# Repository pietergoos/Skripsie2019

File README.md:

# Skripsie2019
Final year project / Thesis

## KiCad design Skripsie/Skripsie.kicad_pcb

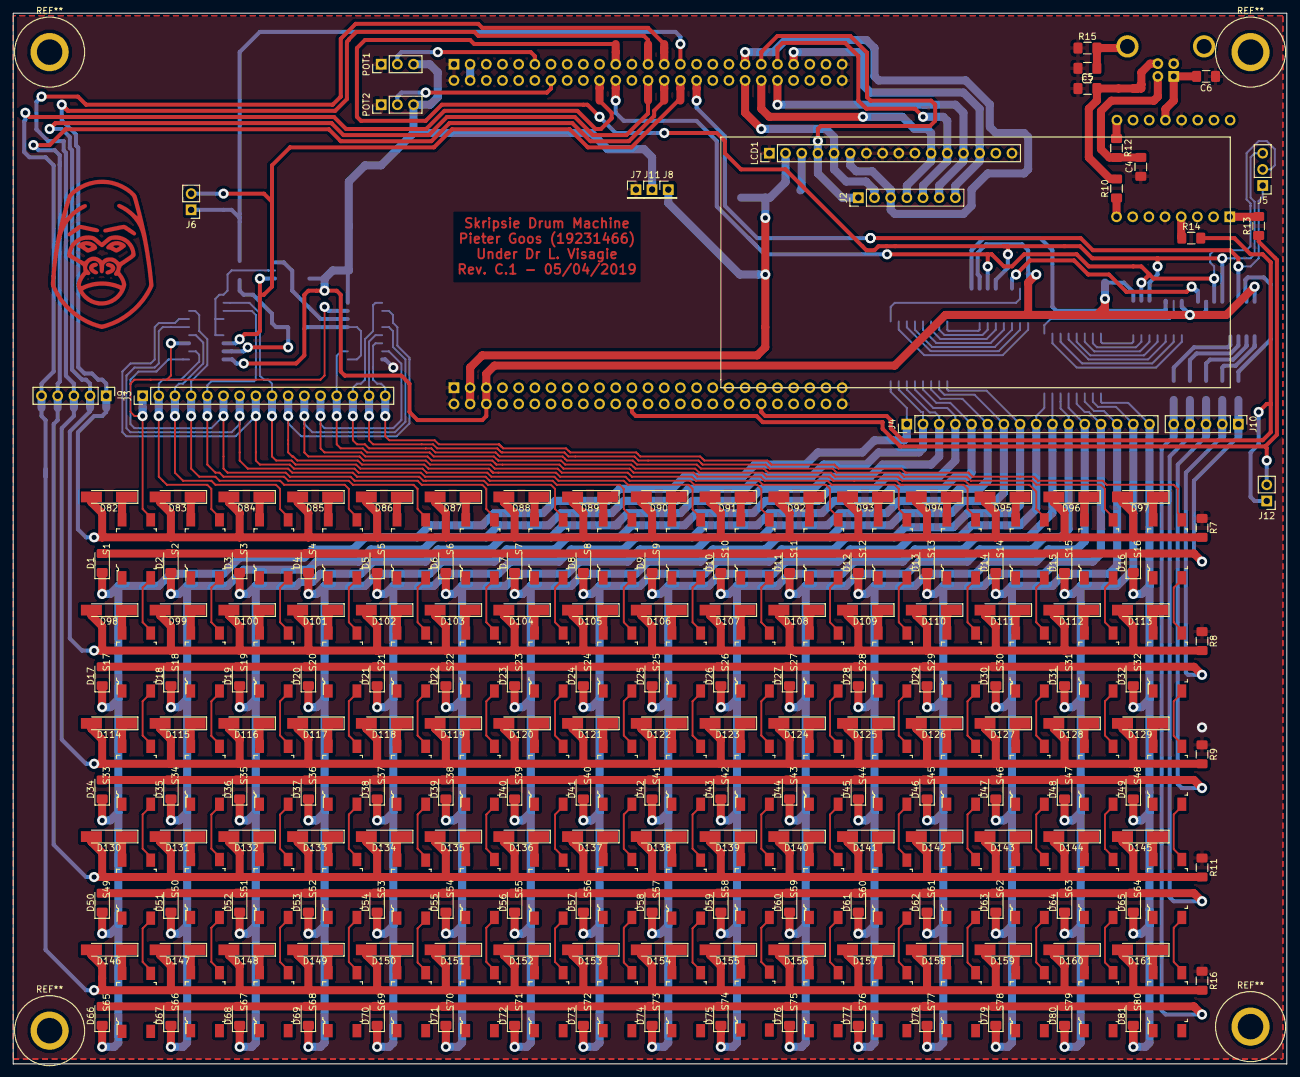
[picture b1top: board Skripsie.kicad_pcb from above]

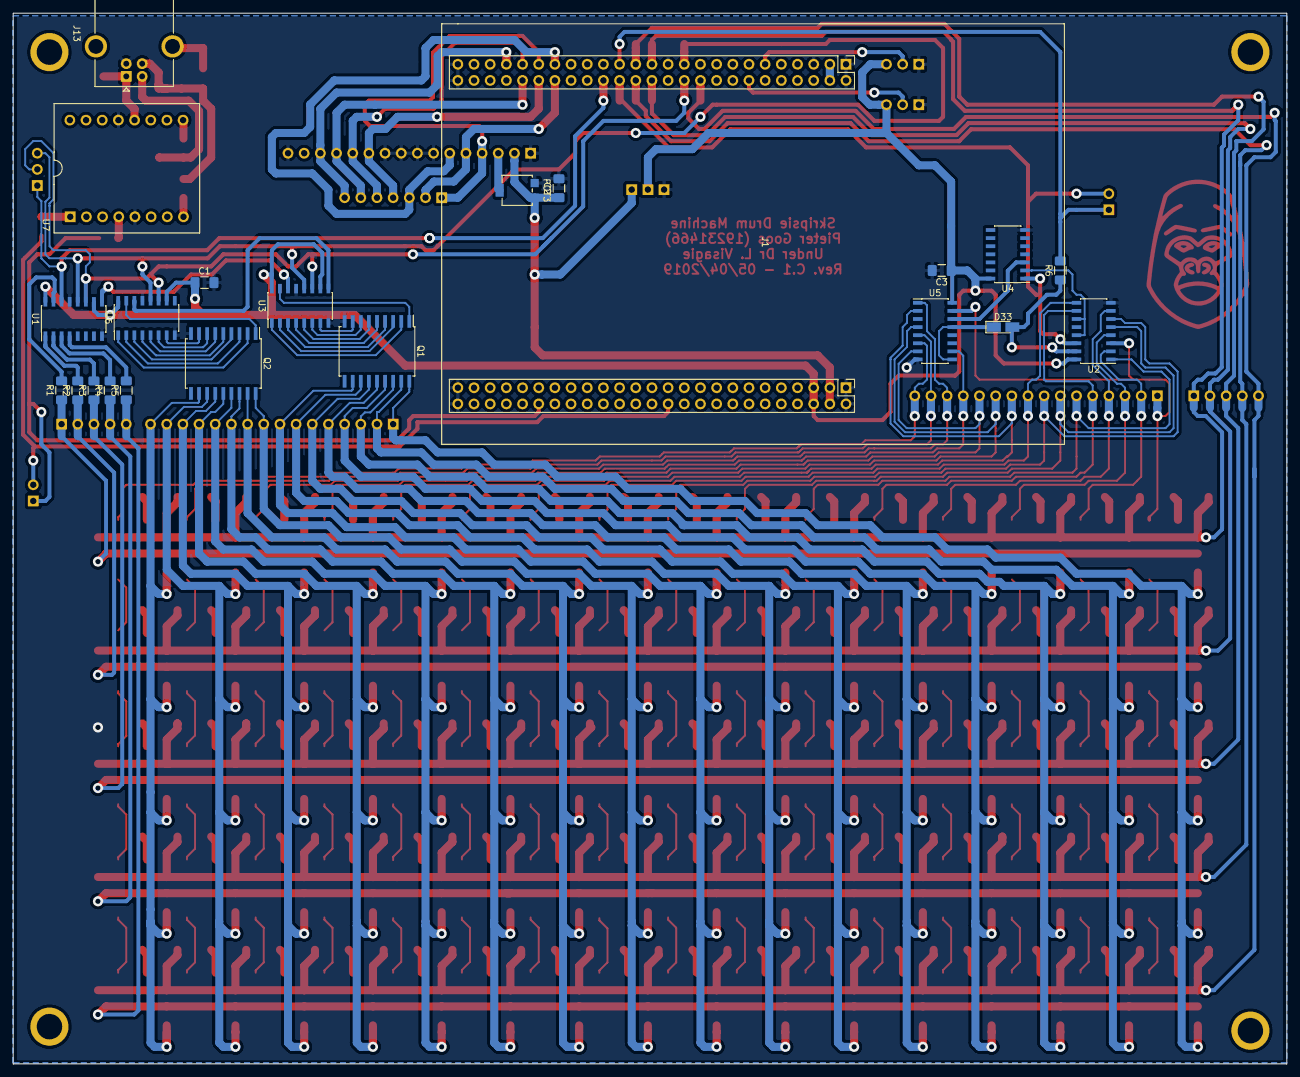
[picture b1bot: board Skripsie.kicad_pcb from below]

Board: 2 copper layers, 200.0 x 165.0 mm, 290 parts (22 on the bottom side), 178 nets.

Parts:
C1, C2, C3, C6: 10nF; C_1206_3216Metric_Pad1.42x1.75mm_HandSolder
C4, C5: 47pF; C_1206_3216Metric_Pad1.42x1.75mm_HandSolder
C7: 1nF; C_1206_3216Metric_Pad1.42x1.75mm_HandSolder
D1, D2, D3, D4, D5, D6, D7, D8, D9, D10, D11, D12, D13, D14, D15, D16, D17, D18, D19, D20, D21, D22, D23, D24, D25, D26, D27, D28, D29, D30, D31, D32, D34, D35, D36, D37, D38, D39, D40, D41, D42, D43, D44, D45, D46, D47, D48, D49, D50, D51, D52, D53, D54, D55, D56, D57, D58, D59, D60, D61, D62, D63, D64, D65, D66, D67, D68, D69, D70, D71, D72, D73, D74, D75, D76, D77, D78, D79, D80, D81: LTST-C150KFKT; LED_1206_3216Metric_Pad1.42x1.75mm_HandSolder
D33: FDLL4148; D_MicroMELF_Hadsoldering
D82, D83, D84, D85, D86, D87, D88, D89, D90, D91, D92, D93, D94, D95, D96, D97, D98, D99, D100, D101, D102, D103, D104, D105, D106, D107, D108, D109, D110, D111, D112, D113, D114, D115, D116, D117, D118, D119, D120, D121, D122, D123, D124, D125, D126, D127, D128, D129, D130, D131, D132, D133, D134, D135, D136, D137, D138, D139, D140, D141, D142, D143, D144, D145, D146, D147, D148, D149, D150, D151, D152, D153, D154, D155, D156, D157, D158, D159, D160, D161: FDLL4148; D_MiniMELF_Handsoldering
J1: STM32F4_Discovery; PinHeader_2x25_P2.54mm_Vertical
J2: LCD_TEST; PinHeader_1x07_P2.54mm_Vertical
J3: BTN_C_TEST; PinHeader_1x16_P2.54mm_Vertical
J4: LED_C_TEST; PinHeader_1x16_P2.54mm_Vertical
J5: LED_SER_TEST; PinHeader_1x03_P2.54mm_Vertical
J6: BTN_SER_TEST; PinHeader_1x02_P2.54mm_Vertical
J7: GND; PinHeader_1x01_P2.54mm_Vertical
J8: 5V; PinHeader_1x01_P2.54mm_Vertical
J9: BTN_R_TEST; PinHeader_1x05_P2.54mm_Vertical
J10: LED_R_TEST; PinHeader_1x05_P2.54mm_Vertical
J11: 3V3; PinHeader_1x01_P2.54mm_Vertical
J12: UART_TEST; PinHeader_1x02_P2.54mm_Vertical
J13: USB_B; USB_B_OST_USB-B1HSxx_Horizontal
LCD1: PC1601A
POT1, POT2: 10KE; PinHeader_1x03_P2.54mm_Vertical
POT3: 20KE; Potentiometer_Bourns_3314G_Vertical
Q1, Q2: ULN2803ADWR; SOIC-18W_7.5x11.6mm_P1.27mm
R1, R2, R3, R4, R5: 47E; R_1206_3216Metric_Pad1.42x1.75mm_HandSolder
R6, R13, R14: 1K; R_1206_3216Metric_Pad1.42x1.75mm_HandSolder
R7, R8, R9, R11, R16: 10K; R_1206_3216Metric_Pad1.42x1.75mm_HandSolder
R10, R12: 27E; R_1206_3216Metric_Pad1.42x1.75mm_HandSolder
R15: 1M; R_1206_3216Metric_Pad1.42x1.75mm_HandSolder
S1, S2, S3, S4, S5, S6, S7, S8, S9, S10, S11, S12, S13, S14, S15, S16, S17, S18, S19, S20, S21, S22, S23, S24, S25, S26, S27, S28, S29, S30, S31, S32, S33, S34, S35, S36, S37, S38, S39, S40, S41, S42, S43, S44, S45, S46, S47, S48, S49, S50, S51, S52, S53, S54, S55, S56, S57, S58, S59, S60, S61, S62, S63, S64, S65, S66, S67, S68, S69, S70, S71, S72, S73, S74, S75, S76, S77, S78, S79, S80: TACT_BTN; Switch_Tactile_SMD_6x6mm
U1, U3, U6: SN74HC595; SOIC-16_3.9x9.9mm_P1.27mm
U2, U5: CD74HC4017; SOIC-16_3.9x9.9mm_P1.27mm
U4: SN74HC08N; SOIC-14_3.9x8.7mm_P1.27mm
U7: FT230XS-U; FT230XS-HEADER

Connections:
+3V3: C1.1, C3.1, J1.53, J1.98, J11.1, POT1.3, POT2.3, U1.10, U1.16, U2.16, U3.10, U3.16, U4.14, U5.16, U6.10, U6.16
+5V: C2.1, J1.52, J1.99, J8.1, LCD1.2, POT3.1
ADC_TEMPO: J1.44, POT2.2
ADC_VOLUME: J1.6, POT1.2
BTN_R0: D82.2, D83.2, D84.2, D85.2, D86.2, D87.2, D88.2, D89.2, D90.2, D91.2, D92.2, D93.2, D94.2, D95.2, D96.2, D97.2, J1.13, J9.1, R7.2
BTN_R1: D98.2, D99.2, D100.2, D101.2, D102.2, D103.2, D104.2, D105.2, D106.2, D107.2, D108.2, D109.2, D110.2, D111.2, D112.2, D113.2, J1.38, J9.2, R8.2
BTN_R2: D114.2, D115.2, D116.2, D117.2, D118.2, D119.2, D120.2, D121.2, D122.2, D123.2, D124.2, D125.2, D126.2, D127.2, D128.2, D129.2, J1.14, J9.3, R9.2
BTN_R3: D130.2, D131.2, D132.2, D133.2, D134.2, D135.2, D136.2, D137.2, D138.2, D139.2, D140.2, D141.2, D142.2, D143.2, D144.2, D145.2, J1.37, J9.4, R11.2
BTN_R4: D146.2, D147.2, D148.2, D149.2, D150.2, D151.2, D152.2, D153.2, D154.2, D155.2, D156.2, D157.2, D158.2, D159.2, D160.2, D161.2, J1.41, J9.5, R16.2
BTN_RESET: J1.15, J6.1, R6.2
BTN_SRCLK: J1.36, J6.2, U2.14, U4.1
GND: C1.2, C2.2, C3.2, C4.1, C5.1, C6.1, C7.2, J1.1, J1.3, J1.12, J1.25, J1.26, J1.50, J1.51, J1.75, J1.76, J1.100, J7.1, J13.4, LCD1.1, LCD1.7, LCD1.8, LCD1.9, LCD1.10, LCD1.16, POT1.1, POT2.1, POT3.3, Q1.9, Q2.9, R7.1, R8.1, R9.1, R11.1, R15.1, R16.1, U1.8, U1.13, U2.8, U3.8, U3.13, U4.7, U5.8, U6.8, U6.13, U7.5, U7.13
LCD_DB4: J1.31, J2.4, LCD1.11
LCD_DB5: J1.21, J2.5, LCD1.12
LCD_DB6: J1.30, J2.6, LCD1.13
LCD_DB7: J1.22, J2.7, LCD1.14
LCD_E: J1.19, J2.3, LCD1.6
LCD_RNW: J1.32, J2.2, LCD1.5
LCD_RS: J1.20, J2.1, LCD1.4
LED_RCLK: J1.11, J5.3, U1.12, U3.12, U6.12
LED_SERIAL: J1.35, J5.1, U1.14
LED_SRCLK: J1.40, J5.2, U1.11, U3.11, U6.11
unnamed: C4.2, J13.2, R12.2
unnamed: C5.2, J13.3, R10.2
unnamed: C6.2, J13.1, U7.12
unnamed: C7.1, J13.5, R15.2
unnamed: D33.1, U5.9, U5.13
unnamed: D33.2, R6.1, U2.15
unnamed: D82.1, S1.1
unnamed: D83.1, S2.1
unnamed: D84.1, S3.1
unnamed: D85.1, S4.1
unnamed: D86.1, S5.1
unnamed: D87.1, S6.1
unnamed: D88.1, S7.1
unnamed: D89.1, S8.1
unnamed: D90.1, S9.1
unnamed: D91.1, S10.1
unnamed: D92.1, S11.1
unnamed: D93.1, S12.1
unnamed: D94.1, S13.1
unnamed: D95.1, S14.1
unnamed: D96.1, S15.1
unnamed: D97.1, S16.1
unnamed: D98.1, S17.1
unnamed: D99.1, S18.1
unnamed: D100.1, S19.1
unnamed: D101.1, S20.1
unnamed: D102.1, S21.1
unnamed: D103.1, S22.1
unnamed: D104.1, S23.1
unnamed: D105.1, S24.1
unnamed: D106.1, S25.1
unnamed: D107.1, S26.1
unnamed: D108.1, S27.1
unnamed: D109.1, S28.1
unnamed: D110.1, S29.1
unnamed: D111.1, S30.1
unnamed: D112.1, S31.1
unnamed: D113.1, S32.1
unnamed: D114.1, S33.1
unnamed: D115.1, S34.1
unnamed: D116.1, S35.1
unnamed: D117.1, S36.1
unnamed: D118.1, S37.1
unnamed: D119.1, S38.1
unnamed: D120.1, S39.1
unnamed: D121.1, S40.1
unnamed: D122.1, S41.1
unnamed: D123.1, S42.1
unnamed: D124.1, S43.1
unnamed: D125.1, S44.1
unnamed: D126.1, S45.1
unnamed: D127.1, S46.1
unnamed: D128.1, S47.1
unnamed: D129.1, S48.1
unnamed: D130.1, S49.1
unnamed: D131.1, S50.1
unnamed: D132.1, S51.1
unnamed: D133.1, S52.1
unnamed: D134.1, S53.1
unnamed: D135.1, S54.1
unnamed: D136.1, S55.1
unnamed: D137.1, S56.1
unnamed: D138.1, S57.1
unnamed: D139.1, S58.1
unnamed: D140.1, S59.1
unnamed: D141.1, S60.1
unnamed: D142.1, S61.1
unnamed: D143.1, S62.1
unnamed: D144.1, S63.1
unnamed: D145.1, S64.1
unnamed: D146.1, S65.1
unnamed: D147.1, S66.1
unnamed: D148.1, S67.1
unnamed: D149.1, S68.1
unnamed: D150.1, S69.1
unnamed: D151.1, S70.1
unnamed: D152.1, S71.1
unnamed: D153.1, S72.1
unnamed: D154.1, S73.1
unnamed: D155.1, S74.1
unnamed: D156.1, S75.1
unnamed: D157.1, S76.1
unnamed: D158.1, S77.1
unnamed: D159.1, S78.1
unnamed: D160.1, S79.1
unnamed: D161.1, S80.1
unnamed: LCD1.3, POT3.2
unnamed: Q1.1, U3.15
unnamed: Q1.2, U3.1
unnamed: Q1.3, U3.2
unnamed: Q1.4, U3.3
unnamed: Q1.5, U3.4
unnamed: Q1.6, U3.5
unnamed: Q1.7, U3.6
unnamed: Q1.8, U3.7
unnamed: Q2.1, U6.15
unnamed: Q2.2, U6.1
unnamed: Q2.3, U6.2
unnamed: Q2.4, U6.3
unnamed: Q2.5, U6.4
unnamed: Q2.6, U6.5
unnamed: Q2.7, U6.6
unnamed: Q2.8, U6.7
unnamed: R1.2, U1.15
unnamed: R2.2, U1.1
unnamed: R3.2, U1.2
unnamed: R4.2, U1.3
unnamed: R5.2, U1.4
unnamed: R10.1, U7.8
unnamed: R12.1, U7.9
unnamed: R13.2, U7.1
unnamed: R14.1, U7.4
unnamed: U1.9, U3.14
unnamed: U2.11, U2.13, U4.2
unnamed: U3.9, U6.14
unnamed: U4.3, U5.14
USART1_RX: J1.89, J12.2, R13.1
USART1_TX: J1.81, J12.1, R14.2
USB_5V: J1.2, J1.49, J1.90
bc0: J3.1, S1.2, S17.2, S33.2, S49.2, S65.2, U2.3, U5.15
bc1: J3.2, S2.2, S18.2, S34.2, S50.2, S66.2, U2.2
bc2: J3.3, S3.2, S19.2, S35.2, S51.2, S67.2, U2.4
bc3: J3.4, S4.2, S20.2, S36.2, S52.2, S68.2, U2.7
bc4: J3.5, S5.2, S21.2, S37.2, S53.2, S69.2, U2.10
bc5: J3.6, S6.2, S22.2, S38.2, S54.2, S70.2, U2.1
bc6: J3.7, S7.2, S23.2, S39.2, S55.2, S71.2, U2.5
bc7: J3.8, S8.2, S24.2, S40.2, S56.2, S72.2, U2.6
bc8: J3.9, S9.2, S25.2, S41.2, S57.2, S73.2, U2.9
bc9: J3.10, S10.2, S26.2, S42.2, S58.2, S74.2, U5.2
bc10: J3.11, S11.2, S27.2, S43.2, S59.2, S75.2, U5.4
bc11: J3.12, S12.2, S28.2, S44.2, S60.2, S76.2, U5.7
bc12: J3.13, S13.2, S29.2, S45.2, S61.2, S77.2, U5.10
bc13: J3.14, S14.2, S30.2, S46.2, S62.2, S78.2, U5.1
bc14: J3.15, S15.2, S31.2, S47.2, S63.2, S79.2, U5.5
bc15: J3.16, S16.2, S32.2, S48.2, S64.2, S80.2, U5.6
c0: D1.1, D17.1, D34.1, D50.1, D66.1, J4.1, Q1.18
c1: D2.1, D18.1, D35.1, D51.1, D67.1, J4.2, Q1.17
c2: D3.1, D19.1, D36.1, D52.1, D68.1, J4.3, Q1.16
c3: D4.1, D20.1, D37.1, D53.1, D69.1, J4.4, Q1.15
c4: D5.1, D21.1, D38.1, D54.1, D70.1, J4.5, Q1.14
c5: D6.1, D22.1, D39.1, D55.1, D71.1, J4.6, Q1.13
c6: D7.1, D23.1, D40.1, D56.1, D72.1, J4.7, Q1.12
c7: D8.1, D24.1, D41.1, D57.1, D73.1, J4.8, Q1.11
c8: D9.1, D25.1, D42.1, D58.1, D74.1, J4.9, Q2.18
c9: D10.1, D26.1, D43.1, D59.1, D75.1, J4.10, Q2.17
c10: D11.1, D27.1, D44.1, D60.1, D76.1, J4.11, Q2.16
c11: D12.1, D28.1, D45.1, D61.1, D77.1, J4.12, Q2.15
c12: D13.1, D29.1, D46.1, D62.1, D78.1, J4.13, Q2.14
c13: D14.1, D30.1, D47.1, D63.1, D79.1, J4.14, Q2.13
c14: D15.1, D31.1, D48.1, D64.1, D80.1, J4.15, Q2.12
c15: D16.1, D32.1, D49.1, D65.1, D81.1, J4.16, Q2.11
r0: D1.2, D2.2, D3.2, D4.2, D5.2, D6.2, D7.2, D8.2, D9.2, D10.2, D11.2, D12.2, D13.2, D14.2, D15.2, D16.2, J10.1, R1.1
r1: D17.2, D18.2, D19.2, D20.2, D21.2, D22.2, D23.2, D24.2, D25.2, D26.2, D27.2, D28.2, D29.2, D30.2, D31.2, D32.2, J10.2, R2.1
r2: D34.2, D35.2, D36.2, D37.2, D38.2, D39.2, D40.2, D41.2, D42.2, D43.2, D44.2, D45.2, D46.2, D47.2, D48.2, D49.2, J10.3, R3.1
r3: D50.2, D51.2, D52.2, D53.2, D54.2, D55.2, D56.2, D57.2, D58.2, D59.2, D60.2, D61.2, D62.2, D63.2, D64.2, D65.2, J10.4, R4.1
r4: D66.2, D67.2, D68.2, D69.2, D70.2, D71.2, D72.2, D73.2, D74.2, D75.2, D76.2, D77.2, D78.2, D79.2, D80.2, D81.2, J10.5, R5.1

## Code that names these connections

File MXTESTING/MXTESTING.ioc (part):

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Mcu.Name=STM32F411V(C-E)Tx
Mcu.Package=LQFP100
Mcu.UserName=STM32F411VETx
PA0-WKUP.GPIOParameters=GPIO_ModeDefaultEXTI
PA0-WKUP.GPIO_ModeDefaultEXTI=GPIO_MODE_EVT_RISING
PA0-WKUP.Signal=GPXTI0
PA1.GPIOParameters=GPIO_Label
PA1.GPIO_Label=ADC_VOLUME
PA1.Signal=ADCx_IN1
PA10.GPIOParameters=GPIO_Label
PA10.GPIO_Label=OTG_FS_ID
PA10.Signal=USB_OTG_FS_ID
PA11.GPIOParameters=GPIO_Label
PA11.GPIO_Label=OTG_FS_DM
PA11.Mode=Host_Only
PA11.Signal=USB_OTG_FS_DM
PA12.GPIOParameters=GPIO_Label
PA12.GPIO_Label=OTG_FS_DP
PA12.Mode=Host_Only
PA12.Signal=USB_OTG_FS_DP
PA13.GPIOParameters=GPIO_Label
PA13.GPIO_Label=SWDIO
PA13.Mode=Serial_Wire
PA13.Signal=SYS_JTMS-SWDIO
PA14.GPIOParameters=GPIO_Label
PA14.GPIO_Label=SWCLK
PA14.Mode=Serial_Wire
PA14.Signal=SYS_JTCK-SWCLK
PA15.Mode=Asynchronous
PA15.Signal=USART1_TX
PA2.GPIOParameters=GPIO_Label
PA2.GPIO_Label=ADC_TEMPO
PA2.Signal=ADCx_IN2
PA4.GPIOParameters=GPIO_Speed,GPIO_PuPd,GPIO_Label,GPIO_Mode
PA4.GPIO_Label=I2S3_WS [CS43L22_LRCK]
PA4.GPIO_Mode=GPIO_MODE_AF_PP
PA4.GPIO_PuPd=GPIO_NOPULL
PA4.GPIO_Speed=GPIO_SPEED_FREQ_LOW
PA4.Mode=Half_Duplex_Master
PA4.Signal=I2S3_WS
PA5.GPIOParameters=GPIO_Label
PA5.GPIO_Label=SPI1_SCK [L3GD20_SC/SPC]
PA5.Mode=Full_Duplex_Master
PA5.Signal=SPI1_SCK
PA6.GPIOParameters=GPIO_Label
PA6.GPIO_Label=SPI1_MISO [L3GD20_AS0/SDO]
PA6.Mode=Full_Duplex_Master
PA6.Signal=SPI1_MISO
PA7.GPIOParameters=GPIO_Label
PA7.GPIO_Label=SPI1_MOSI [L3GD20_SDA/SDI/SDO]
PA7.Mode=Full_Duplex_Master
PA7.Signal=SPI1_MOSI
PA9.GPIOParameters=GPIO_Label
PA9.GPIO_Label=VBUS_FS
PA9.Signal=USB_OTG_FS_VBUS
PB0.GPIOParameters=GPIO_PuPd,GPIO_Label
PB0.GPIO_Label=LED_SRCLK
PB0.GPIO_PuPd=GPIO_NOPULL
PB0.Mode=Simplex_Bidirectional_Master
PB0.Signal=SPI5_SCK
PB1.GPIOParameters=GPIO_Label
PB1.GPIO_Label=LED_RCLK
PB1.Signal=GPIO_Output
PB10.GPIOParameters=GPIO_Label
PB10.GPIO_Label=CLK_IN [MP45DT02_CLK]
PB10.Mode=Full_Duplex_Master
PB10.Signal=I2S2_CK
PB12.Mode=Full_Duplex_Master
PB12.Signal=I2S2_WS
PB13.GPIOParameters=GPIO_Label
PB13.GPIO_Label=LCD_E
PB13.Signal=GPIO_Output
PB14.GPIOParameters=GPIO_Label
PB14.GPIO_Label=LCD_RNW
PB14.Signal=GPIO_Output
PB15.GPIOParameters=GPIO_Label
PB15.GPIO_Label=LCD_RS
PB15.Signal=GPIO_Output
PB3.GPIOParameters=GPIO_Label
PB3.GPIO_Label=SWO
PB3.Signal=SYS_JTDO-SWO
PB6.GPIOParameters=GPIO_Speed,GPIO_PuPd,GPIO_Label,GPIO_Mode
PB6.GPIO_Label=Audio_SCL [CS43L22_SCL]
PB6.GPIO_Mode=GPIO_MODE_AF_OD
PB6.GPIO_PuPd=GPIO_NOPULL
PB6.GPIO_Speed=GPIO_SPEED_FREQ_LOW
PB6.Mode=I2C
PB6.Signal=I2C1_SCL
PB7.Mode=Asynchronous
PB7.Signal=USART1_RX
PB9.GPIOParameters=GPIO_Speed,GPIO_PuPd,GPIO_Label,GPIO_Mode
PB9.GPIO_Label=Audio_SDA [CS43L22_SDA]
PB9.GPIO_Mode=GPIO_MODE_AF_OD
PB9.GPIO_PuPd=GPIO_NOPULL
PB9.GPIO_Speed=GPIO_SPEED_FREQ_LOW
PB9.Mode=I2C
PB9.Signal=I2C1_SDA
PC0.GPIOParameters=PinState,GPIO_Label
PC0.GPIO_Label=OTG_FS_PowerSwitchOn
PC0.PinState=GPIO_PIN_SET
PC0.Signal=GPIO_Output
PC10.GPIOParameters=GPIO_Speed,GPIO_PuPd,GPIO_Label,GPIO_Mode
PC10.GPIO_Label=I2S3_SCK [CS43L22_SCLK]
PC10.GPIO_Mode=GPIO_MODE_AF_PP
PC10.GPIO_PuPd=GPIO_NOPULL
PC10.GPIO_Speed=GPIO_SPEED_FREQ_LOW
PC10.Mode=Half_Duplex_Master
PC10.Signal=I2S3_CK
PC12.GPIOParameters=GPIO_Speed,GPIO_PuPd,GPIO_Label,GPIO_Mode
PC12.GPIO_Label=I2S3_SD [CS43L22_SDIN]
PC12.GPIO_Mode=GPIO_MODE_AF_PP
PC12.GPIO_PuPd=GPIO_NOPULL
PC12.GPIO_Speed=GPIO_SPEED_FREQ_LOW
PC12.Mode=Half_Duplex_Master
PC12.Signal=I2S3_SD
PC14-OSC32_IN.GPIOParameters=GPIO_Label
PC14-OSC32_IN.GPIO_Label=PC14-OSC32_IN
PC14-OSC32_IN.Signal=RCC_OSC32_IN
PC15-OSC32_OUT.GPIOParameters=GPIO_Label
PC15-OSC32_OUT.GPIO_Label=PC15-OSC32_OUT
PC15-OSC32_OUT.Signal=RCC_OSC32_OUT
PC2.Mode=Full_Duplex_Master
PC2.Signal=I2S2_ext_SD
PC3.GPIOParameters=GPIO_Label
PC3.GPIO_Label=PDM_OUT [MP45DT02_DOUT]
PC3.Mode=Full_Duplex_Master
PC3.Signal=I2S2_SD
PC4.GPIOParameters=GPIO_Label
PC4.GPIO_Label=BTN_R4
PC4.Signal=GPIO_Input
PC7.GPIOParameters=GPIO_Speed,GPIO_PuPd,GPIO_Label,GPIO_Mode
PC7.GPIO_Label=I2S3_MCK [CS43L22_MCLK]
PC7.GPIO_Mode=GPIO_MODE_AF_PP
PC7.GPIO_PuPd=GPIO_NOPULL
PC7.GPIO_Speed=GPIO_SPEED_FREQ_LOW
PC7.Mode=Master_Clock_Activated
PC7.Signal=I2S3_MCK
PD10.GPIOParameters=GPIO_Label
PD10.GPIO_Label=LCD_DB6
PD10.Signal=GPIO_Output
PD11.GPIOParameters=GPIO_Label
PD11.GPIO_Label=LCD_DB7
PD11.Signal=GPIO_Output
PD12.GPIOParameters=GPIO_Speed,GPIO_PuPd,GPIO_Label
PD12.GPIO_Label=LD4 [Green Led]
PD12.GPIO_PuPd=GPIO_NOPULL
PD12.GPIO_Speed=GPIO_SPEED_FREQ_LOW
PD12.Signal=GPIO_Output
PD13.GPIOParameters=GPIO_Speed,GPIO_PuPd,GPIO_Label
PD13.GPIO_Label=LD3 [Orange Led]
PD13.GPIO_PuPd=GPIO_NOPULL
PD13.GPIO_Speed=GPIO_SPEED_FREQ_LOW
PD13.Signal=GPIO_Output
PD14.GPIOParameters=GPIO_Speed,GPIO_PuPd,GPIO_Label
PD14.GPIO_Label=LD5 [Red Led]
PD14.GPIO_PuPd=GPIO_NOPULL
PD14.GPIO_Speed=GPIO_SPEED_FREQ_LOW
PD14.Signal=GPIO_Output
PD15.GPIOParameters=GPIO_Speed,GPIO_PuPd,GPIO_Label
PD15.GPIO_Label=LD6 [Blue Led]
PD15.GPIO_PuPd=GPIO_NOPULL
PD15.GPIO_Speed=GPIO_SPEED_FREQ_LOW
PD15.Signal=GPIO_Output
PD4.GPIOParameters=GPIO_Label
PD4.GPIO_Label=Audio_RST [CS43L22_RESET]
PD4.Signal=GPIO_Output
PD5.GPIOParameters=GPIO_Label
PD5.GPIO_Label=OTG_FS_OverCurrent
PD5.Signal=GPIO_Input
PD8.GPIOParameters=GPIO_Label
PD8.GPIO_Label=LCD_DB4
PD8.Signal=GPIO_Output
PD9.GPIOParameters=GPIO_Label
PD9.GPIO_Label=LCD_DB5
PD9.Signal=GPIO_Output
PE1.GPIOParameters=GPIO_Label,GPIO_ModeDefaultEXTI
PE1.GPIO_Label=MEMS_INT2 [L3GD20_INT2]
PE1.GPIO_ModeDefaultEXTI=GPIO_MODE_EVT_RISING
PE1.Signal=GPXTI1
PE10.GPIOParameters=GPIO_Label
PE10.GPIO_Label=BTN_R3
PE10.Signal=GPIO_Input
PE11.GPIOParameters=GPIO_Label
PE11.GPIO_Label=BTN_RESET
PE11.Signal=GPIO_Output
PE12.GPIOParameters=GPIO_Label
PE12.GPIO_Label=BTN_CLK
PE12.Signal=GPIO_Output
PE14.GPIOParameters=GPIO_PuPd,GPIO_Label
PE14.GPIO_Label=LED_SERIAL
PE14.GPIO_PuPd=GPIO_NOPULL
PE14.Mode=Simplex_Bidirectional_Master
PE14.Signal=SPI5_MOSI
PE2.GPIOParameters=GPIO_Label
PE2.GPIO_Label=DATA_Ready [LSM303DLHC_DRDY]
PE2.Signal=GPIO_Input
PE3.GPIOParameters=GPIO_Label
PE3.GPIO_Label=CS_I2C/SPI [L3GD20_CS_I2C/SPI]
PE3.Signal=GPIO_Output
PE4.GPIOParameters=GPIO_Label,GPIO_ModeDefaultEXTI
PE4.GPIO_Label=INT1 [LSM303DLHC_INT1]
PE4.GPIO_ModeDefaultEXTI=GPIO_MODE_EVT_RISING
PE4.Signal=GPXTI4
PE5.GPIOParameters=GPIO_Label,GPIO_ModeDefaultEXTI
PE5.GPIO_Label=INT2 [LSM303DLHC_INT2]
PE5.GPIO_ModeDefaultEXTI=GPIO_MODE_EVT_RISING
PE5.Signal=GPXTI5
PE7.GPIOParameters=GPIO_Label
PE7.GPIO_Label=BTN_R0
PE7.Signal=GPIO_Input
PE8.GPIOParameters=GPIO_Label
PE8.GPIO_Label=BTN_R1
PE8.Signal=GPIO_Input
PE9.GPIOParameters=GPIO_Label
PE9.GPIO_Label=BTN_R2
PE9.Signal=GPIO_Input
PH0\ -\ OSC_IN.GPIOParameters=GPIO_Label
PH0\ -\ OSC_IN.GPIO_Label=PH0-OSC_IN
PH0\ -\ OSC_IN.Mode=HSE-External-Oscillator
PH0\ -\ OSC_IN.Signal=RCC_OSC_IN
PH1\ -\ OSC_OUT.GPIOParameters=GPIO_Label
PH1\ -\ OSC_OUT.GPIO_Label=PH1-OSC_OUT
PH1\ -\ OSC_OUT.Mode=HSE-External-Oscillator
PH1\ -\ OSC_OUT.Signal=RCC_OSC_OUT
RCC.HSE_VALUE=8000000
RCC.SYSCLKFreq_VALUE=84000000
RCC.SYSCLKSource=RCC_SYSCLKSOURCE_PLLCLK
board=32F411EDISCOVERY
boardIOC=true

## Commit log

2019-02-21 Added Given Example
2019-02-21 TrueStudio directory changed
2019-02-21 Changed code to open the file 5 times - pre test
2019-02-21 Rebuilt code and fixed spelling error
2019-02-22 5 Streams load now but play out of sync
2019-02-22 Final adjustments made - Audio error is due to differing lengths ~ issue to solve later
2019-02-23 Arduino Code for testing arrays added
2019-02-23 Added report template
2019-02-26 Added KiCAD files
2019-02-27 Updated Schematic
2019-02-27 Cube MX set up
2019-02-28 Corrected LED Driver circuit for REV A
2019-03-01 Altered LED Driver and Button driver circuits - Rev B
2019-03-01 Added forgotten files
2019-03-04 Added new pinout file & reset mechanism for Button driver
2019-03-04 Corrected Diode orientation
2019-03-05 Updated the schematic and ordered parts
2019-03-06 Updated footprint link with symbols; Started PCB Design - completed button/led array.
2019-03-07 Update to majority of PCB
2019-03-07 PCB complete before infill
2019-03-07 Adjusted traces for more efficiency
2019-03-07 Further corrections
2019-03-07 Infill Added to PCB
2019-03-09 Gerber files added along with text and a symbol
2019-03-13 Latex template updated
2019-03-13 LED driving code prototype added
2019-03-27 Corrected PCB Missing Traces & Updated to Rev C
2019-04-01 History added, new name, full system diagram
2019-04-01 Removed blankspace and commented out code
2019-04-03 Arduino Code for testing LED matrix
2019-04-03 Created project in CubeMX and have rows appearing on LED matrix
2019-04-04 Timer function found and implemented - rows iterate per second
2019-04-04 SPI5 changed to LSB first and adjusted the row select to match
2019-04-04 Row rendering for LED inverted and array for matrix now used
2019-04-04 LED array driving functions added
2019-04-04 Button Code added and SPI removed in favour of manual toggling
2019-04-05 Button Row 4 changed from PB2 to PC4 due to onboard resistors
2019-04-05 PB2 -> PC4 and voltage test points moved to more logical position
2019-04-06 UART1 and ADC1.1 and ADC1.2 enabled and reading data using DMA
2019-04-06 Preliminary tempo control implemented and UART commented out (issues with pc due to speed)
2019-04-08 LCD Panel Code Added with BPM and Volume Calcs
2019-04-10 Added audio libraries and moved h files to inc folder
2019-04-10 Added further needed imports
2019-04-11 Corrections made to systick usage
2019-04-21 Added BSP files for audio handling. Basic functions created however, unused and without prototype
2019-04-24 Added "workings" to run USB - doesn't seem to work
2019-04-25 Basic File Reading working and audio scheduling correct. Gibberish output
2019-04-25 Added Testing folder for CubeMX
2019-04-25 Audio plays back but seems segmented between channels (noise with low tones in one, high tones in other)
2019-04-30 Minor fixes - Files not reading fast enough
2019-05-08 Changed to using new CS43L22 driver, works now, audio not ending at correct time
2019-05-09 Corrected filesize variable as was seeing as 8b instead of 16b vals; Volume code corrected as mute was not quiet enough
2019-05-10 Further report work w/ schedule
2019-06-06 Final Push
